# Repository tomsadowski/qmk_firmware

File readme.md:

## pearbear qmk firmware project directory

This is a fork of the qmk_firmware repo for hosting the pearbear keyboard. All other keyboards have been removed from this fork. If you would like to keep your qmk_firmware repo, simply add the keyboards/pearbear to your keyboards directory.

If you have a pearbear and need to flash it, start by referring to the official instructions for installing the qmk framework from the QMK website. Once QMK is installed, continue with the instructions below.

#### set your config as follows:
- $: qmk config compile.keyboard=pearbear
- $: qmk config compile.keymap=tomsadowski
- $: qmk config flash.keyboard=pearbear
- $: qmk config flash.keymap=tomsadowski

#### compile:   
- $: qmk compile

#### flash left: 
- plug USB into left half.
- $: qmk flash -bl uf2-split-left
- on the left half, press and hold the Boot Button on the KeyBoar circuit for 6 seconds while tapping the Reset Button 3 times. wait for indication in terminal that flashing is in progress before letting go.

#### flash right: 
- plug USB into right half.
- $: qmk flash -bl uf2-split-right
- on the right half, press and hold the Boot Button on the KeyBoar circuit for 6 seconds while tapping the Reset Button 3 times. wait for indication in terminal that flashing is in progress before letting go.

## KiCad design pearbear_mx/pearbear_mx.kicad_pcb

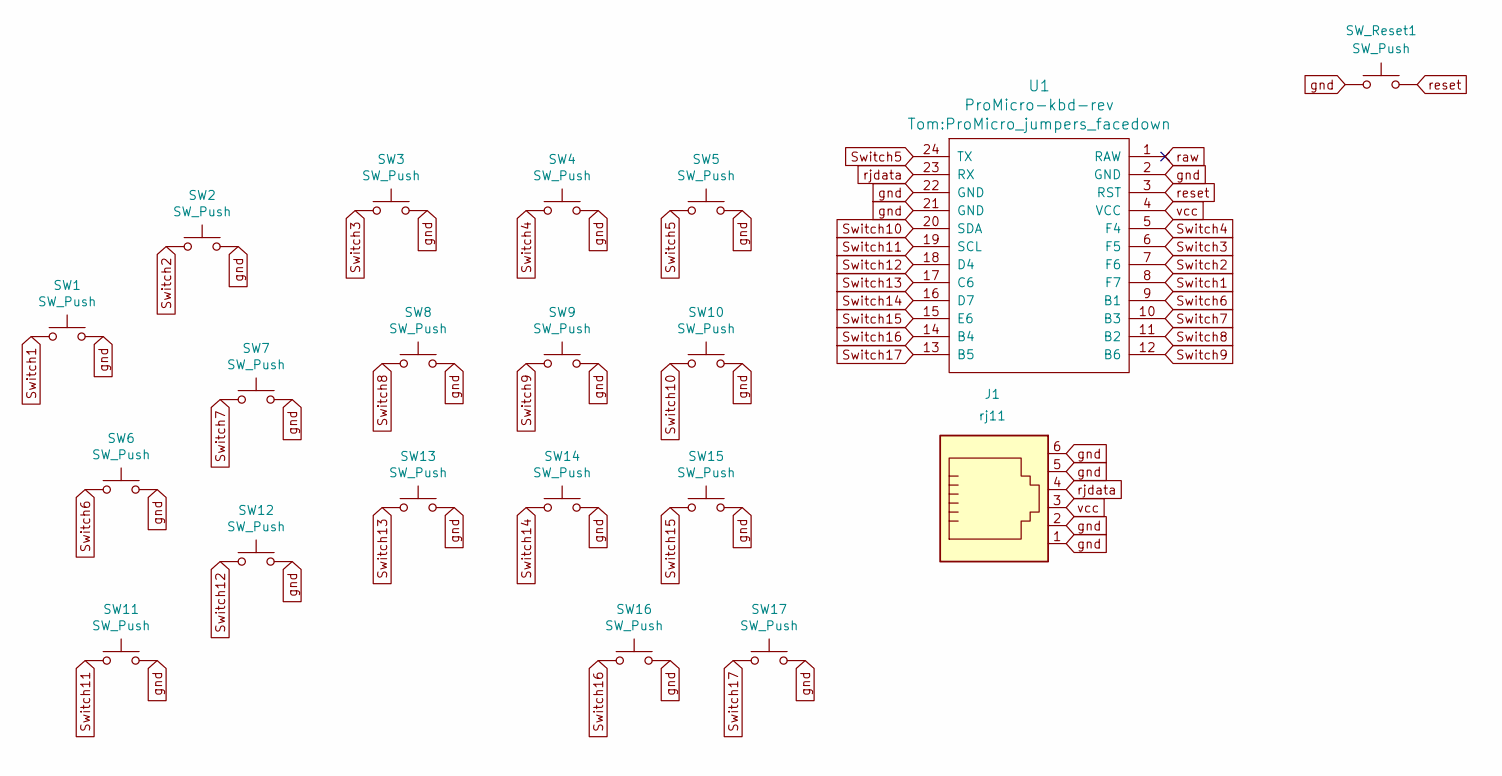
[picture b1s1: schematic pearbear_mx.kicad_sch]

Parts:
J1: rj11; RJ12_Amphenol_54601_vert_reversible_1
SW1, SW2, SW3, SW4, SW5, SW6, SW7, SW8, SW9, SW10, SW11, SW12, SW13, SW14, SW15, SW16, SW17: SW_Push; SW_Cherry_MX_1.00u_PCB_reversible
SW_Reset1: SW_Push; SW_TH_Tactile_Omron_B3F-10xx_reversible
U1: ProMicro-kbd-rev; ProMicro_jumpers_facedown

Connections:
Switch1: SW1.1, U1.8 (F7)
Switch2: SW2.1, U1.7 (F6)
Switch3: SW3.1, U1.6 (F5)
Switch4: SW4.1, U1.5 (F4)
Switch5: SW5.1, U1.24 (TX)
Switch6: SW6.1, U1.9 (B1)
Switch7: SW7.1, U1.10 (B3)
Switch8: SW8.1, U1.11 (B2)
Switch9: SW9.1, U1.12 (B6)
Switch10: SW10.1, U1.20 (SDA)
Switch11: SW11.1, U1.19 (SCL)
Switch12: SW12.1, U1.18 (D4)
Switch13: SW13.1, U1.17 (C6)
Switch14: SW14.1, U1.16 (D7)
Switch15: SW15.1, U1.15 (E6)
Switch16: SW16.1, U1.14 (B4)
Switch17: SW17.1, U1.13 (B5)
gnd: J1.1, J1.2, J1.5, J1.6, SW1.2, SW2.2, SW3.2, SW4.2, SW5.2, SW6.2, SW7.2, SW8.2, SW9.2, SW10.2, SW11.2, SW12.2, SW13.2, SW14.2, SW15.2, SW16.2, SW17.2, SW_Reset1.1, U1.2 (GND), U1.21 (GND), U1.22 (GND)
raw: U1.1 (RAW)
raw_0: U1.1 (RAW)
raw_1: U1.1 (RAW)
raw_2: U1.1 (RAW)
raw_3: U1.1 (RAW)
reset: SW_Reset1.2, U1.3 (RST)
rjdata: J1.4, U1.23 (RX)
vcc: J1.3, U1.4 (VCC)

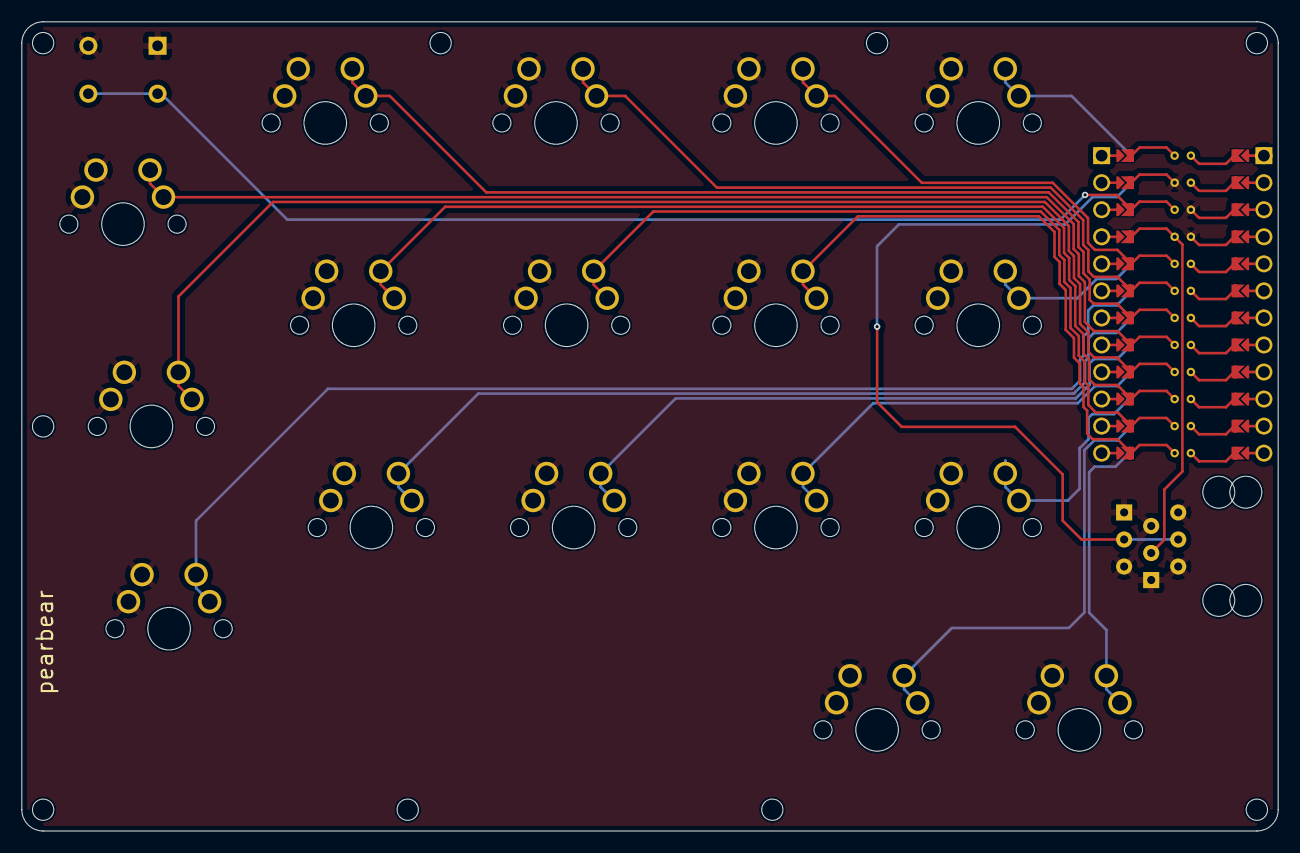
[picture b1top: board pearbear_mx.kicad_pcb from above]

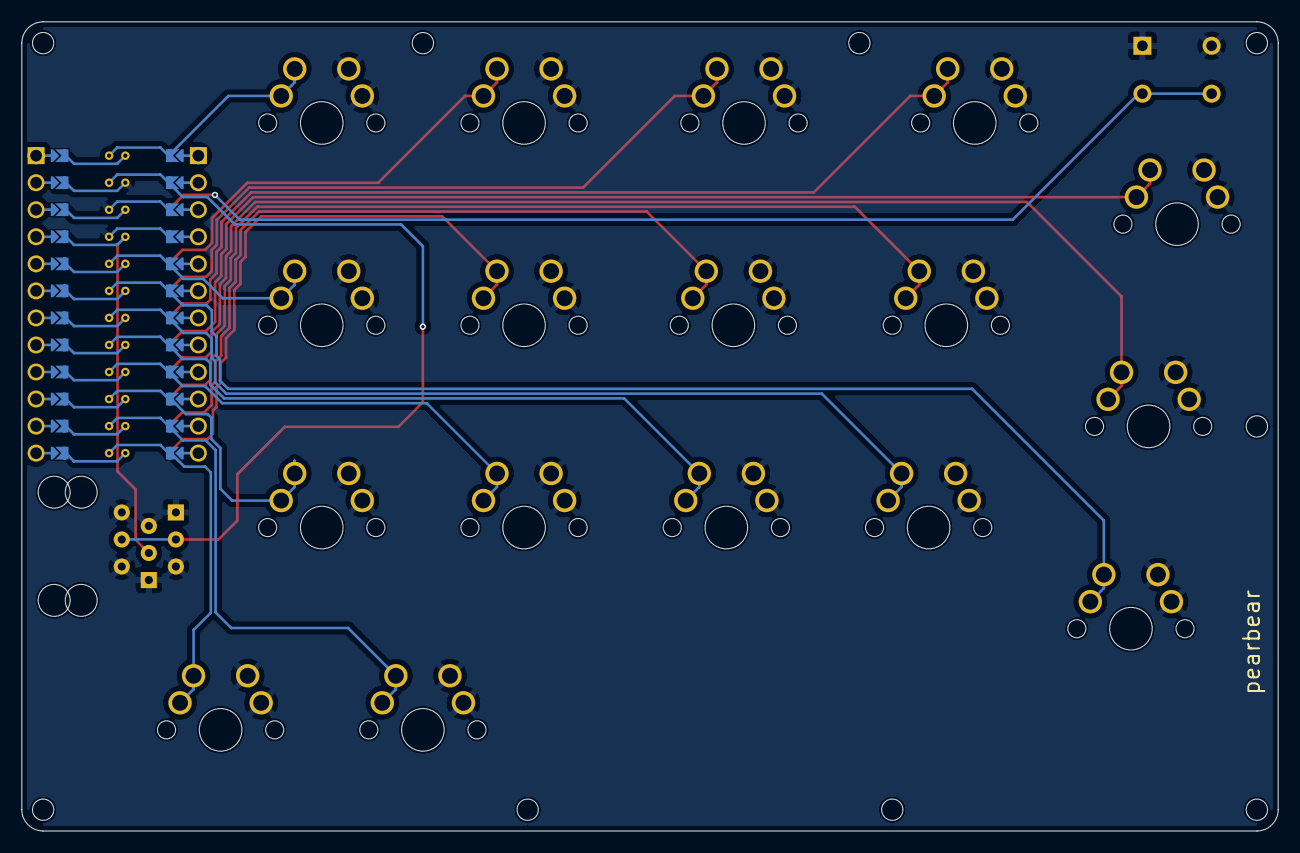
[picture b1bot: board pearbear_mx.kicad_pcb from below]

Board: 2 copper layers, 118.0 x 76.0 mm, 20 parts (19 on the bottom side), 21 nets.

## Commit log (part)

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2024-06-21 things
2024-06-21 cleanup
2024-06-21 cleanliness
2024-06-24 release gate fun
2024-06-25 very refactor
2024-06-25 this should work
2024-06-25 more
2024-06-25 things2
2024-06-25 poop
2024-06-25 tommy
2024-06-25 removed stuff i will never use
2024-06-25 changed things
2024-06-26 docs
2024-06-26 docs but more
2024-06-26 names
2024-06-26 names2
2024-06-26 it is time
2024-06-28 pearbear
2025-11-03 pearbear added, removed the rest
2025-11-05 readme updates
2025-11-06 include pics for documentation
